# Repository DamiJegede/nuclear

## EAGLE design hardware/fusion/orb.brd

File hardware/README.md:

## Current routed engineering draft — Rev D (2026-10-29)

Four-layer routing and antenna clearance clipped to the circular edge. **Fusion confirms zero airwires, zero copper-clearance errors and zero overlap errors.** Saved as **Orb Mainboard Rev D - Routed**. Two matched-length errors and forty wire-stub warnings remain; this is not a fabrication release. See [routing-rev-d.md](design/routing-rev-d.md) for current checks, required filled-and-capped vias and fabrication holds. Routing is reproducible through `src/routing.json`; do not regenerate from older Rev C sources. Earlier sections below record the previous revision.

# Current board revision: C

U1 is now ESP32-C3FH4X with a separate 40 MHz crystal and Johanson 2450AT18D0100001E SMT antenna. GPIO assignments and 23-LED count are preserved. See [RF redesign notes](design/rf-redesign.md). Generated files are the revised schematic and placement draft; the Rev B Fusion archive remains an earlier routing checkpoint.

# Orb hardware

The Orb main board: a 69 mm round board with an ESP32-C3-MINI-1-N4X, a PN7161 NFC controller, 23 WS2812B LEDs on a ring (R31.5), a MAX98357A amplifier, USB-C, and a 1-cell Li-ion charger, gauge and 3.3 V supply. Product decisions are in `docs/ORB.md`; this folder turns them into files you can open in Fusion.

## Import into Fusion

Written for Autodesk Fusion (Electronics). The files are in the Eagle XML format, which Fusion imports. The initial files were imported and linked in Fusion on 2026-10-29. The source revision below corrects problems found by the initial Fusion DRC; confirm the revised import and its DRC before release.

1. Fusion's Data Panel, **Upload**, and choose all three files from `hardware/fusion/`: `orb.lbr`, `orb.sch`, `orb.brd`. (Or File, Open, Open from my computer.)
2. Open `orb.sch`: 122 parts in functional blocks (MCU, USB, power, I2C, NFC, audio, LED rail, LED ring), every connection a named net.
3. Open `orb.brd`: the R34.5 mm outline and the layout below, all connections unrouted (ratsnest). `design/layout.png` is a picture of it.
4. Run ERC on the schematic and DRC on the board. Expect warnings: the footprint list in `design/open-items.md` is the reason for most.

## Layout revision 2026-10-29

- **LEDs:** 23 on R31.5, clockwise: upper right 65/52/39/26/13 degrees; lower arc -12 to -168 degrees in 13-degree steps (13 LEDs); upper left 167/154/141/128/115 degrees. Five on each upper side, with a 50-degree opening around USB-C at 12 o'clock. Measured minimum LED copper-pad gap: 0.309 mm (the former 12-degree arrangement overlapped).
- **USB-C:** remains underneath at 12 o'clock. Manufacturer drawing-based pad rows and slotted mounts replace the former SMD-only approximation. The manufacturer's front-face/PCB-edge reference is aligned at y=34.5; the former guessed 2.7 mm overhang is removed. Mount holes and their copper annuli reserve clearance on both faces. Slot plating/geometry and the enclosure opening still need fabrication/mechanical review.
- **Speaker:** mounted directly on the PCB as requested; a 15 x 11 mm body, with 19.5 x 12 mm total assembly allowance, is reserved at (0,9). This part uses solder pads and adhesive retention with short hand-soldered leads; a reflow mounting specification is not available. Polymer capacitors move to (-10,21.6)/(10,21.6), battery header to (0,20.5), MCU to (-9.4,-5.2). Smaller parts are repacked around these bodies.
- **FPC:** Hirose FH19C-4S-0.5SH(10), 0.5 mm pitch, bottom contacts, 0.2 mm tail. Mouth +y, origin (0,-20.5); positions 2/3 carry RF, 1/4 remain open. Confirm tail fabrication stack-up.
- **Preserved constraints:** 69 mm circular board, M2 holes at (+-32,0), pedestal slots at (+-27.4,0), pedestal keep-outs on both sides, clear branding area below y=-22.5. Battery stays underneath; the LED decouplers are underneath their LEDs. The top USB gap now leaves their through mounts clear.
- `src/layout.py` checks courtyards and mechanical restrictions. `design/geometry-audit.json` records the separate source-file copper audit. Fusion DRC/ERC and actual routing are still required; this is an engineering draft.

## What is solid and what is not

- **Solid:** pin and pad numbers of every IC, taken from the manufacturers' datasheets (ESP32-C3-MINI-1 v2.2, PN7160/PN7161 rev 4.2, BQ2407x, TPS63802, TPS22918, SN74LV1T34, MAX98357A, MAX17048); all connections; the GPIO plan; the resistor arithmetic (3.3 V divider, charge and input limits, VBUS sense). `src/check.py` and `src/verify_eagle.py` prove those.
- **Still preliminary:** USB-C plated-slot fabrication, speaker assembly/retention, generic NFC/amplifier/gauge footprints, LED revision and passive MPN/height selection require review. Manufacturer-derived overrides replace U1/J1/J2/J3/U4/U5 geometry; the NFC matching network and crystal remain TBD. See `design/open-items.md`.
- **Still requires engineering validation:** antenna tuning and certification.

## Files

| Path | What |
| --- | --- |
| `fusion/orb.lbr`, `orb.sch`, `orb.brd` | Generated. Do not edit by hand; edit `src/design.py` and rebuild |
| `components/` | 19 downloaded standalone STEP models, source manifest and licenses; see `components/README.md` for generic/provisional models and unresolved parts |
| `bom/bom.csv` | Bill of materials: part, quantity, references, value, package, manufacturer, MPN, status (specified / generic / TBD) |
| `design/pin-plan.md` | GPIO assignments with the datasheet reasons |
| `design/power.md` | Power tree, part choices and the current budget |
| `design/open-items.md` | What must still happen before fabrication |
| `src/design.py` | The single source of truth: part types (pins by datasheet), instances, nets, GPIO plan |
| `src/check.py` | Checks the design (pads, nets, GPIOs, strapping rules, arithmetic) |
| `src/layout.py`, `src/preview.py` | Place the parts, check the board rules, draw `design/layout.png` |
| `src/eagle.py`, `build.py` | Write the Fusion files, BOM and pin plan |
| `src/verify_eagle.py` | Re-reads the Fusion files and compares them with the design |

Rebuild: `npm run hardware:build` (runs the check, writes everything, then verifies the written files).

## Decisions made while building this (change them in `design.py`)

- **PN7161 on I2C** (order code PN7161A1HN/C101E), sharing the bus with the fuel gauge, because the module exposes only 15 GPIOs and the board needs 14 signals; SPI would not fit. The firmware's four SPI pin constants are gone.
- **BQ24074** charger with power path (VSYS follows the battery, 4.4 V on USB), **TPS63802** buck-boost for 3.3 V, **TPS22918** switch on the LED rail so 28 idle LEDs do not drain the battery, and an **SN74LV1T34** level translator so the 3.3 V data reaches the LEDs' input threshold at VLED.
- No battery NTC: the charger's TS pin is held with a fixed 10 k resistor, as docs/ORB.md says the pack has none.
- Gauge charge detection and the charger's /CHG line both exist; the firmware can use either.

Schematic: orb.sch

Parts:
ANT1: 2450AT18D0100001E; JOHANSON_2450AT18D
C1, C5, C6, C8, C9, C10, C29, C31: 10uF; C0603
C2, C7, C11, C14, C16, C17, C18, C19, C30, C35, C36, C101, C102, C103, C104, C105, C106, C107, C108, C109, C110, C111, C112, C113, C114, C115, C116, C117, C118, C119, C120, C121, C122, C123: 100nF; C0402
C3, C15, C34, C37, C38: 1uF; C0402
C4, C12, C13: 4.7uF; C0603
C20, C21: 12pF; C0402
C22, C23, C24, C25, C26, C27, C28: TBD; C0402
C32, C33: 100uF; CPOL7343
C39: 10nF; C0402
C40, C41: 16pF; C0402
C42, C43, C44, C45: 1pF; C0402
D1: USBLC6-2SC6; SOT23_6
J1: USB-C; USBC24_TE2345986
J2: BAT; JST_S2B_PH_SM4_TB
J3: NFC antenna; FPC4_PLACEHOLDER
L1: 0.47uH; L2016
L2, L3: TBD; L0402
L4: 2nH; L0402
L5: 24nH; L0402
L6: 2.4nH; L0402
LED1, LED2, LED3, LED4, LED5, LED6, LED7, LED8, LED9, LED10, LED11, LED12, LED13, LED14, LED15, LED16, LED17, LED18, LED19, LED20, LED21, LED22, LED23: WS2812B; WS2812B_5050
R1, R10: 10k; R0402
R3, R12, R18, R19, R20: 100k; R0402
R4, R5: 5.1k; R0402
R6: 120k; R0402
R7: 220k; R0402
R8: 1.8k; R0402
R9: 1.13k; R0402
R11: 560k; R0402
R13, R14: 2.2k; R0402
R15, R16: TBD; R0402
R17: 2k; R0402
R21: 33; R0402
R22, R23: 0; R0402
SPK1: CMS-151103-088SP; SPK_PADS
TP1: EN; TP1MM
TP2: BOOT; TP1MM
TP3: 3V3; TP1MM
TP4: GND; TP1MM
TP5: VSYS; TP1MM
TP6: VBAT; TP1MM
U1: ESP32-C3FH4X; ESP32C3_QFN32
U2: PN7161A1HN/C101E; HVQFN40_6X6
U3: MAX17048G+T10; TDFN8_2X2
U4: BQ24074RGTR; VQFN16_3X3
U5: TPS63802DLAR; VSON10_2X3
U6: MAX98357AETE+T; TQFN16_3X3
U7: TPS22918DBVR; SOT23_6
U8: SN74LV1T34DBVR; SOT23_5
Y1: 27.12MHz; XTAL2016
Y2: 40MHz; ABM8_3225

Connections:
3V3: C1.1, C2.1, C9.1, C10.1, C19.1, C35.1, C36.1, C38.1, C39.1, L4.1, R1.1, R3.1, R11.1, R13.1, R14.1, TP3.1, U1.11 (VDD_RTC), U1.17 (VDD_CPU), U1.31 (VDDA), U1.32 (VDDA), U2.6 (VDD_PAD), U5.6 (VOUT)
AMP_SD: R17.1, U1.28 (TXD0_IO21)
AMP_SD_R: R17.2, R18.1, U6.4 (SD_MODE)
ANT_FEED: ANT1.1 (FEED), C45.1, R22.2
ANT_GND_TUNE: ANT1.3 (TUNE), R23.1
BOOT: TP2.1, U1.15 (IO9)
CC1: J1.A5 (CC1), R4.1
CC2: J1.B5 (CC2), R5.1
CHG_STATUS: R3.2, U1.6 (IO2), U4.9 (CHG)
EN: C3.1, R1.2, TP1.1, U1.7 (EN)
ESP_RF_CHIP: C42.1, L6.1, U1.1 (LNA_IN)
ESP_VDD_RF: C34.1, L4.2, U1.2 (VDD_RF), U1.3 (VDD_RF)
ESP_VDD_SPI: C37.1, U1.18 (VDD_SPI)
ESP_XTAL_DRIVE: C40.1, L5.2, Y2.1
ESP_XTAL_N: C41.1, U1.29 (XTAL_N), Y2.3 (2)
ESP_XTAL_P: L5.1, U1.30 (XTAL_P)
FB_3V3: R11.2, R12.1, U5.4 (FB)
GND: ANT1.2 (GND), ANT1.4 (GND), C1.2, C2.2, C3.2, C4.2, C5.2, C6.2, C7.2, C8.2, C9.2, C10.2, C11.2, C12.2, C13.2, C14.2, C15.2, C16.2, C17.2, C18.2, C19.2, C20.2, C21.2, C22.2, C23.2, C29.2, C30.2, C31.2, C32.2 (N), C33.2 (N), C34.2, C35.2, C36.2, C37.2, C38.2, C39.2, C40.2, C41.2, C42.2, C43.2, C44.2, C45.2, C101.2, C102.2, C103.2, C104.2, C105.2, C106.2, C107.2, C108.2, C109.2, C110.2, C111.2, C112.2, C113.2, C114.2, C115.2, C116.2, C117.2, C118.2, C119.2, C120.2, C121.2, C122.2, C123.2, D1.2 (GND), J1.A1 (GND), J1.A12 (GND), J1.B1 (GND), J1.B12 (GND), J1.S1 (SHIELD), J1.S2 (SHIELD), J1.S3 (SHIELD), J1.S4 (SHIELD), J2.2 (BAT_N), J2.S1 (MECH), J2.S2 (MECH), J3.M1 (MECH), J3.M2 (MECH), LED1.3 (VSS), LED2.3 (VSS), LED3.3 (VSS), LED4.3 (VSS), LED5.3 (VSS), LED6.3 (VSS), LED7.3 (VSS), LED8.3 (VSS), LED9.3 (VSS), LED10.3 (VSS), LED11.3 (VSS), LED12.3 (VSS), LED13.3 (VSS), LED14.3 (VSS), LED15.3 (VSS), LED16.3 (VSS), LED17.3 (VSS), LED18.3 (VSS), LED19.3 (VSS), LED20.3 (VSS), LED21.3 (VSS), LED22.3 (VSS), LED23.3 (VSS), R4.2, R5.2, R7.2, R8.2, R9.2, R10.2, R12.2, R18.2, R19.2, R20.2, R23.2, TP4.1, U1.33 (GND), U2.1 (I2C_ADR0), U2.2 (DWL_REQ), U2.3 (I2C_ADR1), U2.4 (VSS_PAD), U2.9 (VSS_A), U2.20 (VSS_TX), U2.39 (WKUP_REQ), U2.41 (VSS), U3.1 (CTG), U3.4 (GND), U3.6 (QSTRT), U3.9 (GND), U4.4 (CE), U4.6 (EN1), U4.8 (VSS), U4.17 (VSS), U5.2 (MODE), U5.3 (AGND), U5.8 (GND), U6.3 (GND), U6.11 (GND), U6.15 (GND), U6.17 (GND), U7.2 (GND), U8.3 (GND), Y1.2 (GND_A), Y1.4 (GND_B), Y2.2 (GND_A), Y2.4 (GND_B)
I2C_SCL: R14.2, U1.10 (IO5), U2.7 (SCL), U3.7 (SCL)
I2C_SDA: R13.2, U1.9 (IO4), U2.5 (SDA), U3.8 (SDA)
I2S_BCLK: U1.13 (IO7), U6.16 (BCLK)
I2S_DIN: U1.27 (RXD0_IO20), U6.1 (DIN)
I2S_LRCLK: U1.16 (IO10), U6.14 (LRCLK)
ILIM: R8.1, U4.12 (ILIM)
ISET: R9.1, U4.16 (ISET)
LED_CHAIN_1: LED1.2 (DOUT), LED2.4 (DIN)
LED_CHAIN_2: LED2.2 (DOUT), LED3.4 (DIN)
LED_CHAIN_3: LED3.2 (DOUT), LED4.4 (DIN)
LED_CHAIN_4: LED4.2 (DOUT), LED5.4 (DIN)
LED_CHAIN_5: LED5.2 (DOUT), LED6.4 (DIN)
LED_CHAIN_6: LED6.2 (DOUT), LED7.4 (DIN)
LED_CHAIN_7: LED7.2 (DOUT), LED8.4 (DIN)
LED_CHAIN_8: LED8.2 (DOUT), LED9.4 (DIN)
LED_CHAIN_9: LED9.2 (DOUT), LED10.4 (DIN)
LED_CHAIN_10: LED10.2 (DOUT), LED11.4 (DIN)
LED_CHAIN_11: LED11.2 (DOUT), LED12.4 (DIN)
LED_CHAIN_12: LED12.2 (DOUT), LED13.4 (DIN)
LED_CHAIN_13: LED13.2 (DOUT), LED14.4 (DIN)
LED_CHAIN_14: LED14.2 (DOUT), LED15.4 (DIN)
LED_CHAIN_15: LED15.2 (DOUT), LED16.4 (DIN)
LED_CHAIN_16: LED16.2 (DOUT), LED17.4 (DIN)
LED_CHAIN_17: LED17.2 (DOUT), LED18.4 (DIN)
LED_CHAIN_18: LED18.2 (DOUT), LED19.4 (DIN)
LED_CHAIN_19: LED19.2 (DOUT), LED20.4 (DIN)
LED_CHAIN_20: LED20.2 (DOUT), LED21.4 (DIN)
LED_CHAIN_21: LED21.2 (DOUT), LED22.4 (DIN)
LED_CHAIN_22: LED22.2 (DOUT), LED23.4 (DIN)
LED_DATA_0: LED1.4 (DIN), R21.2
LED_DATA_3V3: R20.1, U1.12 (IO6), U8.2 (A)
LED_DATA_BUF: R21.1, U8.4 (Y)
LED_EN: R19.1, U1.8 (IO3), U7.3 (ON)
NFC_ANT_N: C25.2, C26.2, C28.1, J3.3
NFC_ANT_P: C24.2, C26.1, C27.1, J3.2
NFC_EMC1: C22.1, C24.1, L2.2
NFC_EMC2: C23.1, C25.1, L3.2
NFC_IRQ: U1.4 (IO0), U2.8 (IRQ)
NFC_RXC1: C27.2, R15.1
NFC_RXC2: C28.2, R16.1
NFC_RXN: R16.2, U2.15 (RXN)
NFC_RXP: R15.2, U2.16 (RXP)
NFC_TX1: L2.1, U2.21 (TX1)
NFC_TX2: L3.1, U2.19 (TX2)
NFC_VDD: C15.1, C16.1, U2.26 (VDD_A), U2.27 (VDD), U2.31 (VDD_D)
NFC_VDDHF: C18.1, U2.25 (VDD_HF)
NFC_VEN: U1.5 (IO1), U2.10 (VEN)
NFC_VMID: C17.1, U2.17 (VDD_VMID)
NFC_XTAL1: C20.1, U2.30 (XTAL1), Y1.1
NFC_XTAL2: C21.1, U2.29 (XTAL2), Y1.3 (2)
RF_50OHM: C43.1, C44.1, L6.2, R22.1
SPK_N: SPK1.2 (N), U6.10 (OUTN)
SPK_P: SPK1.1, U6.9 (OUTP)
SW1: L1.1, U5.9 (L1)
SW2: L1.2, U5.7 (L2)
TS: R10.1, U4.1 (TS)
USB_DN: D1.4 (IO2_B), U1.25 (IO18)
USB_DN_J: D1.3 (IO2_A), J1.A7 (DN), J1.B7 (DN)
USB_DP: D1.6 (IO1_B), U1.26 (IO19)
USB_DP_J: D1.1 (IO1_A), J1.A6 (DP), J1.B6 (DP)
VBAT: C6.1, C7.1, J2.1 (BAT_P), TP6.1, U3.2 (CELL), U3.3 (VDD), U4.2 (BAT), U4.3 (BAT)
VBUS: C4.1, D1.5 (VBUS), J1.A4 (VBUS), J1.A9 (VBUS), J1.B4 (VBUS), J1.B9 (VBUS), R6.1, U4.13 (IN)
VBUS_SENSE: R6.2, R7.1, U1.14 (IO8)
VDD_TX: C13.1, C14.1, U2.14 (VDD_TX), U2.18 (TVDD_IN), U2.22 (TVDD_IN2)
VLED: C32.1, C33.1, C101.1, C102.1, C103.1, C104.1, C105.1, C106.1, C107.1, C108.1, C109.1, C110.1, C111.1, C112.1, C113.1, C114.1, C115.1, C116.1, C117.1, C118.1, C119.1, C120.1, C121.1, C122.1, C123.1, LED1.1 (VDD), LED2.1 (VDD), LED3.1 (VDD), LED4.1 (VDD), LED5.1 (VDD), LED6.1 (VDD), LED7.1 (VDD), LED8.1 (VDD), LED9.1 (VDD), LED10.1 (VDD), LED11.1 (VDD), LED12.1 (VDD), LED13.1 (VDD), LED14.1 (VDD), LED15.1 (VDD), LED16.1 (VDD), LED17.1 (VDD), LED18.1 (VDD), LED19.1 (VDD), LED20.1 (VDD), LED21.1 (VDD), LED22.1 (VDD), LED23.1 (VDD), U7.5 (QOD), U7.6 (VOUT), U8.5 (VCC)
VSYS: C5.1, C8.1, C11.1, C12.1, C29.1, C30.1, C31.1, TP5.1, U2.12 (VBAT2), U2.13 (VDD_UP), U2.28 (VBAT), U4.5 (EN2), U4.10 (OUT), U4.11 (OUT), U5.1 (EN), U5.10 (VIN), U6.7 (VDD), U6.8 (VDD), U7.1 (VIN)

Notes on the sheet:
Orb main board: generated from hardware/src/design.py, do not edit by hand

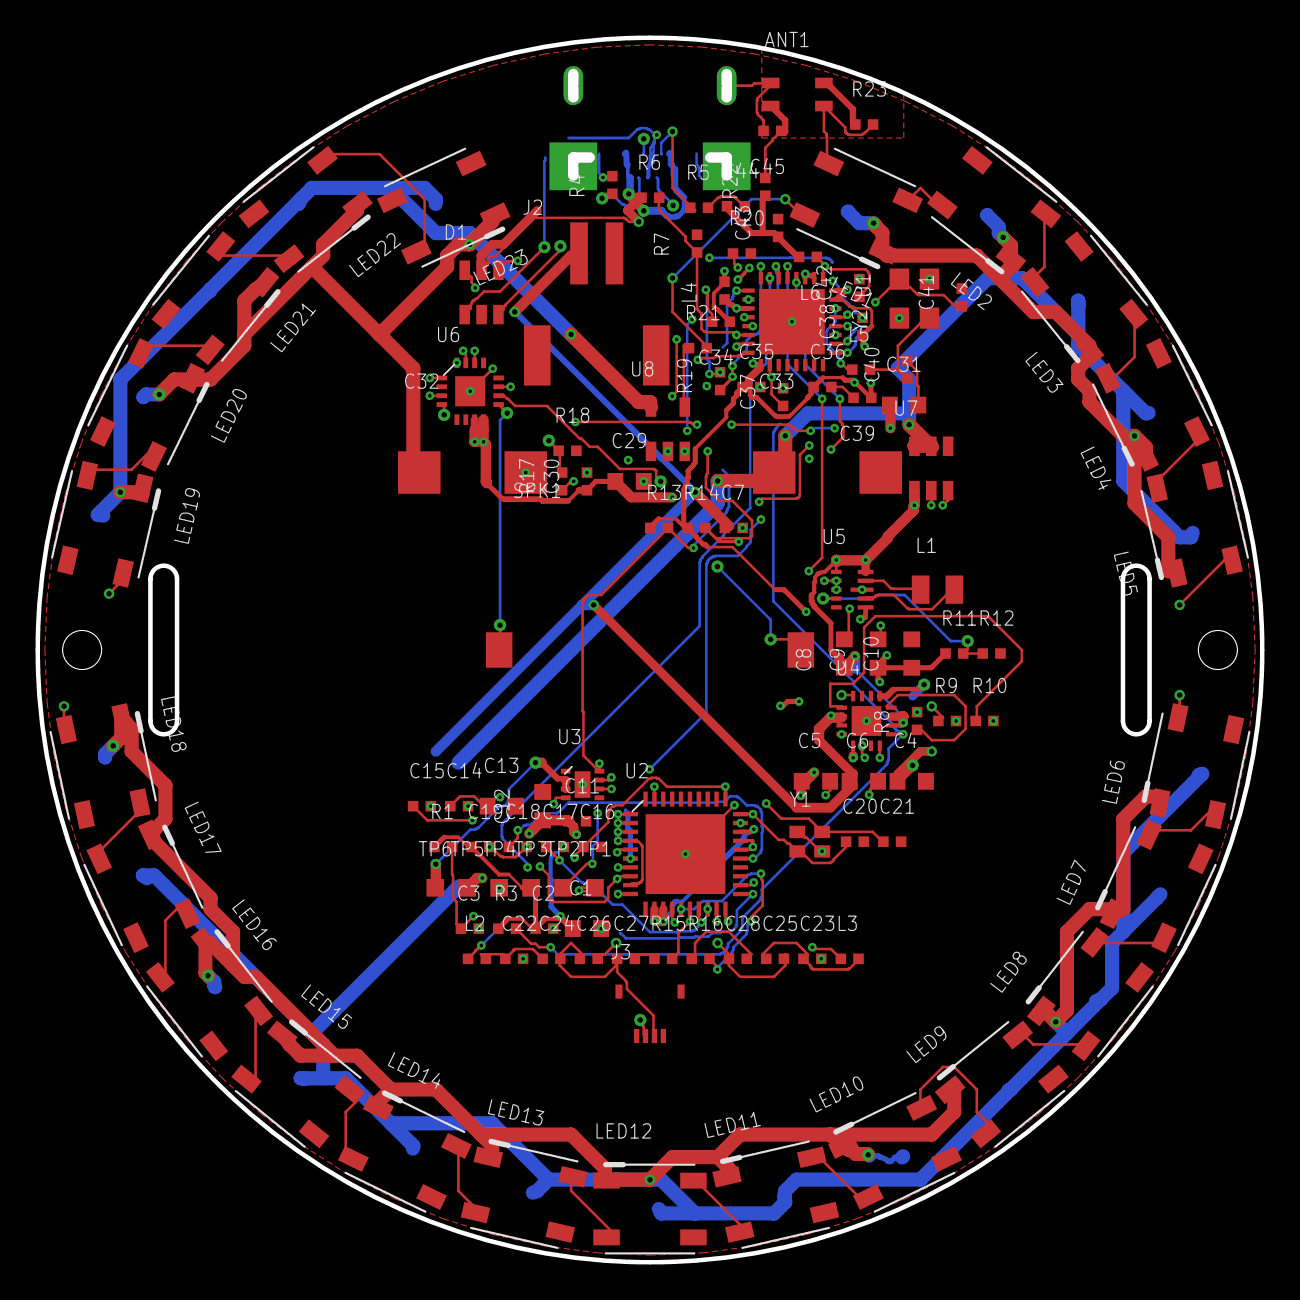
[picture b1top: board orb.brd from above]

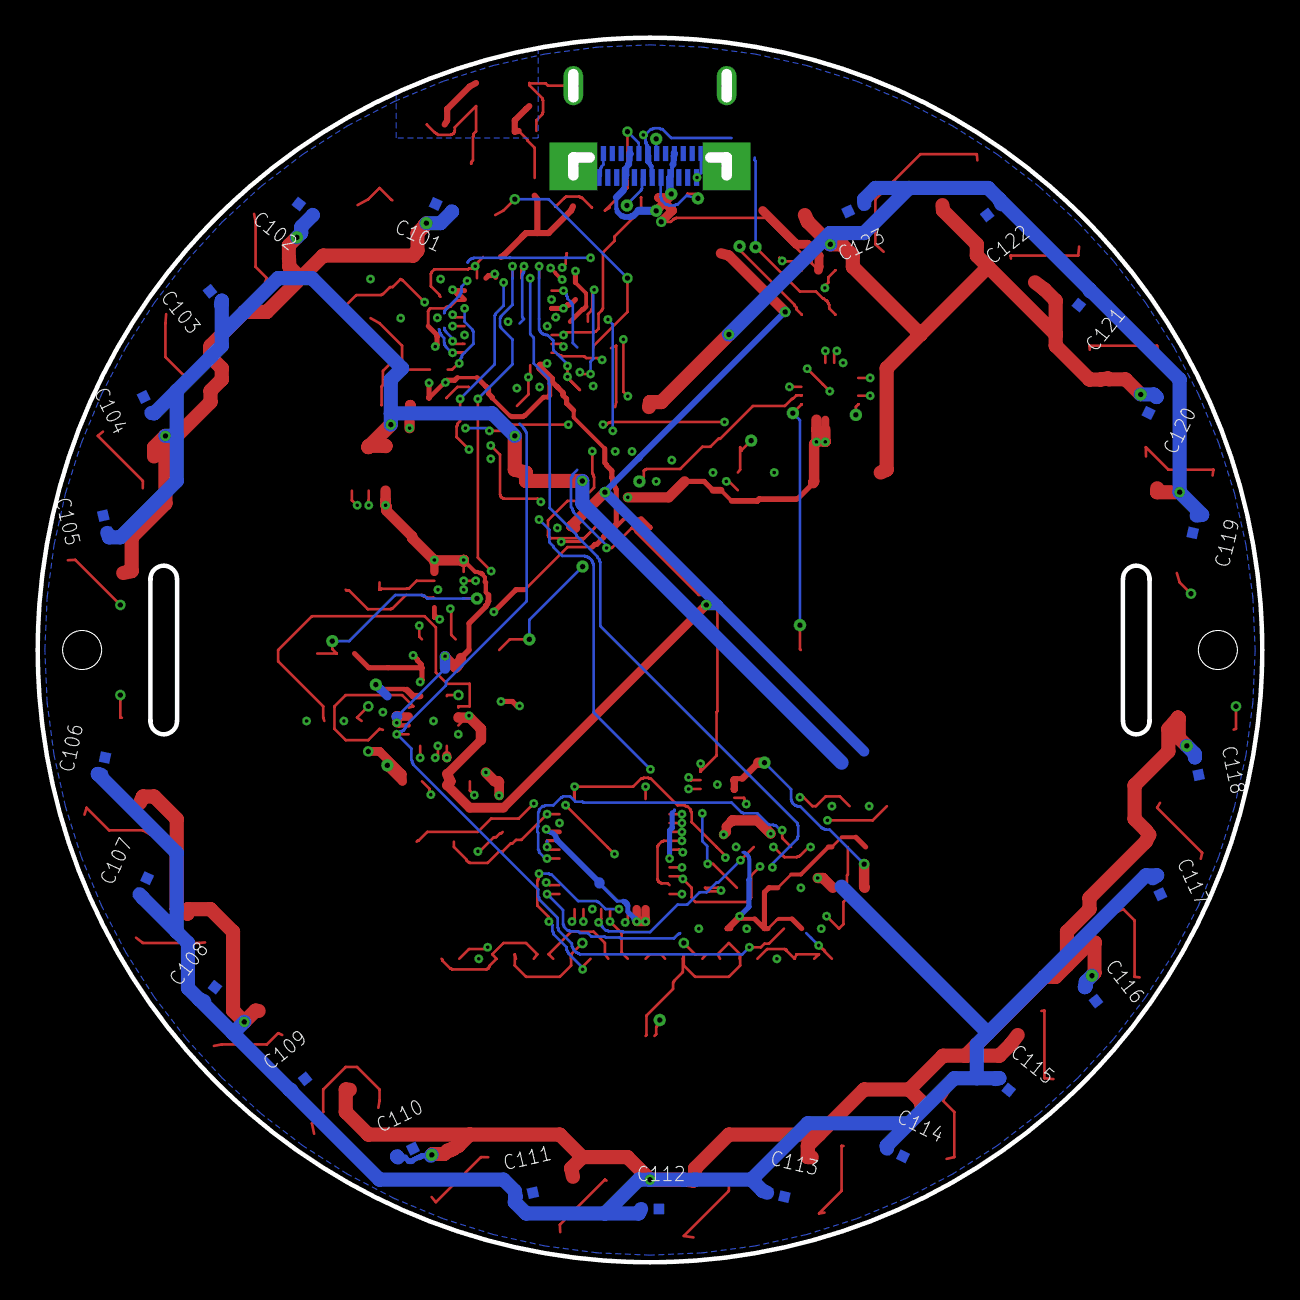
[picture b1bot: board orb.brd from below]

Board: 4 copper layers, 69.0 x 69.0 mm, 141 parts (24 on the bottom side), 84 nets.

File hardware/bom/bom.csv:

Type,Qty,References,Value,Description,Package,Manufacturer,MPN,Status
U,1,U1,ESP32-C3FH4X,"Espressif ESP32-C3FH4X, 4 MB in-package flash, QFN32 5 x 5 mm",ESP32C3_QFN32,Espressif,ESP32-C3FH4X,specified
U,1,U2,PN7161A1HN/C101E,NXP PN7161A1HN NFC controller (I2C),HVQFN40_6X6,NXP,PN7161A1HN/C101E,specified
U,1,U3,MAX17048G+T10,Analog/Maxim MAX17048G+T10 fuel gauge (TDFN-8),TDFN8_2X2,Analog Devices (Maxim),MAX17048G+T10,specified
U,1,U4,BQ24074RGTR,TI BQ24074RGTR charger and power path (VQFN-16),VQFN16_3X3,Texas Instruments,BQ24074RGTR,specified
U,1,U5,TPS63802DLAR,TI TPS63802DLAR buck-boost 3.3 V (VSON-10),VSON10_2X3,Texas Instruments,TPS63802DLAR,specified
U,1,U6,MAX98357AETE+T,Analog/Maxim MAX98357AETE+T I2S Class D amplifier (TQFN-16),TQFN16_3X3,Analog Devices (Maxim),MAX98357AETE+T,specified
U,1,U7,TPS22918DBVR,TI TPS22918DBVR load switch (SOT-23-6),SOT23_6,Texas Instruments,TPS22918DBVR,specified
U,1,U8,SN74LV1T34DBVR,TI SN74LV1T34DBVR level-shifting buffer (SOT-23-5),SOT23_5,Texas Instruments,SN74LV1T34DBVR,specified
J,1,J1,USB-C,"TE Connectivity 2345986-1 USB-C receptacle (24 pads, USB 3.1 top mount, dual row SMT; only the USB 2.0 pads are used)",USBC24_TE2345986,TE Connectivity,2345986-1,specified
J,1,J2,BAT,JST S2B-PH-SM4-TB battery header,JST_S2B_PH_SM4_TB,JST,S2B-PH-SM4-TB,specified
J,1,J3,NFC antenna,"Hirose FH19C-4S-0.5SH(10), 0.5 mm pitch, 0.2 mm bottom-contact FPC",FPC4_PLACEHOLDER,Hirose,FH19C-4S-0.5SH(10),specified
Y,1,Y1,27.12MHz,Crystal,XTAL2016,,,TBD
Y,1,Y2,40MHz,Abracon ABM8 3.2 x 2.5 mm 40 MHz crystal,ABM8_3225,Abracon,ABM8-40.000MHZ-10-1-U-T,specified
D,1,D1,USBLC6-2SC6,ST USBLC6-2SC6 USB ESD protection (SOT-23-6),SOT23_6,STMicroelectronics,USBLC6-2SC6,specified
LED,23,"LED1, LED2, LED3, LED4, LED5, LED6, LED7, LED8, LED9, LED10, LED11, LED12, LED13, LED14, LED15, LED16, LED17, LED18, LED19, LED20, LED21, LED22, LED23",WS2812B,WS2812B addressable LED (5050; revision TBC),WS2812B_5050,Worldsemi,WS2812B,specified
L,1,L1,0.47uH,Power inductor,L2016,,,TBD
L,2,"L2, L3",TBD,Inductor,L0402,,,TBD
L,1,L4,2nH,Inductor,L0402,,,generic
L,1,L5,24nH,Inductor,L0402,,,generic
L,1,L6,2.4nH,Inductor,L0402,,,generic
C,8,"C1, C5, C6, C8, C9, C10, C29, C31",10uF,Capacitor,C0603,,,generic
C,34,"C2, C7, C11, C14, C16, C17, C18, C19, C30, C35, C36, C101, C102, C103, C104, C105, C106, C107, C108, C109, C110, C111, C112, C113, C114, C115, C116, C117, C118, C119, C120, C121, C122, C123",100nF,Capacitor,C0402,,,generic
C,2,"C20, C21",12pF,Capacitor,C0402,,,generic
C,7,"C22, C23, C24, C25, C26, C27, C28",TBD,Capacitor,C0402,,,TBD
C,5,"C3, C15, C34, C37, C38",1uF,Capacitor,C0402,,,generic
C,2,"C32, C33",100uF,Polymer capacitor,CPOL7343,,,generic
C,1,C39,10nF,Capacitor,C0402,,,generic
C,3,"C4, C12, C13",4.7uF,Capacitor,C0603,,,generic
C,2,"C40, C41",16pF,Capacitor,C0402,,,generic
C,2,"C42, C43",1pF,Capacitor,C0402,,,generic
C,2,"C44, C45",1pF,Capacitor,C0402,,,generic
R,2,"R1, R10",10k,Resistor,R0402,,,generic
R,1,R11,560k,Resistor,R0402,,,generic
R,2,"R13, R14",2.2k,Resistor,R0402,,,generic
R,2,"R15, R16",TBD,Resistor,R0402,,,TBD
R,1,R17,2k,Resistor,R0402,,,generic
R,1,R21,33,Resistor,R0402,,,generic
R,2,"R22, R23",0,Resistor,R0402,,,generic
R,5,"R3, R12, R18, R19, R20",100k,Resistor,R0402,,,generic
R,2,"R4, R5",5.1k,Resistor,R0402,,,generic
R,1,R6,120k,Resistor,R0402,,,generic
R,1,R7,220k,Resistor,R0402,,,generic
R,1,R8,1.8k,Resistor,R0402,,,generic
R,1,R9,1.13k,Resistor,R0402,,,generic
T,1,TP1,EN,Test pad,TP1MM,,,generic
T,1,TP2,BOOT,Test pad,TP1MM,,,generic
T,1,TP3,3V3,Test pad,TP1MM,,,generic
T,1,TP4,GND,Test pad,TP1MM,,,generic
T,1,TP5,VSYS,Test pad,TP1MM,,,generic
T,1,TP6,VBAT,Test pad,TP1MM,,,generic
A,1,ANT1,2450AT18D0100001E,"Johanson 2450AT18D0100001E 2.4 GHz SMT antenna, thin-edge reference layout",JOHANSON_2450AT18D,Johanson Technology,2450AT18D0100001E,specified
S,1,SPK1,CMS-151103-088SP,Speaker CMS-151103-088SP (wire or pad connection),SPK_PADS,CUI Devices,CMS-151103-088SP,specified

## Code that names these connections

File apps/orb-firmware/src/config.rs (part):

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/// Enable for the LED power rail (TPS22918): 23 idle LEDs would draw about 23 mA, so the rail is off unless a pattern is showing.
pub const LED_ENABLE_PIN: Option<u8> = Some(3);
/// The PN7161 is the I2C version (PN7161A1HN/C101E): there are no SPI pins. It shares the I2C bus with the fuel gauge.
pub const NFC_IRQ_PIN: Option<u8> = Some(0);
pub const NFC_VEN_PIN: Option<u8> = Some(1);
pub const AUDIO_BCLK_PIN: Option<u8> = Some(7);
pub const AUDIO_LRCLK_PIN: Option<u8> = Some(10);
/// GPIO20 (U0RXD): UART0 is not used, the console is on native USB.
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/// GPIO2 (a strapping pin): the BQ24074 /CHG output, low while charging, with a 100 k pull-up.
pub const CHARGE_STATUS_PIN: Option<u8> = Some(2);
/// The shared I2C bus: PN7161 and MAX17048.
pub const I2C_SDA_PIN: Option<u8> = Some(4);
pub const I2C_SCL_PIN: Option<u8> = Some(5);
/// 7-bit addresses: PN7161 with I2C_ADR0 = I2C_ADR1 = GND, and the MAX17048.
pub const NFC_I2C_ADDRESS: u8 = 0x28;
pub const FUEL_GAUGE_I2C_ADDRESS: u8 = 0x36;
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    use super::*;

    const ASSIGNED: [Option<u8>; 12] = [
        LED_DATA_PIN, LED_ENABLE_PIN, NFC_IRQ_PIN, NFC_VEN_PIN, AUDIO_BCLK_PIN, AUDIO_LRCLK_PIN, AUDIO_DATA_PIN, AUDIO_SHUTDOWN_PIN, USB_POWER_SENSE_PIN,
        CHARGE_STATUS_PIN, I2C_SDA_PIN, I2C_SCL_PIN,
    ];

    #[test]
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
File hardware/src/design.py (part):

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add("C2", "C", "100nF", {"1": "3V3", "2": "GND"}, group="mcu")
add("R1", "R", "10k", {"1": "3V3", "2": "EN"}, group="mcu", note="EN pull-up (datasheet: R=10k, C=1uF RC delay)")
add("C3", "C", "1uF", {"1": "EN", "2": "GND"}, group="mcu")
add("R3", "R", "100k", {"1": "3V3", "2": "CHG_STATUS"}, group="mcu", note="Pull-up for BQ24074 /CHG (open drain) and for GPIO2, which the datasheet recommends pulling high")
add("TP1", "TP", "EN", {"TP": "EN"}, group="mcu", note="Reset pad: short to GND to reset")
add("TP2", "TP", "BOOT", {"TP": "BOOT"}, group="mcu", note="IO9: short to GND at reset for download mode (USB-JTAG/serial)")
add("TP3", "TP", "3V3", {"TP": "3V3"}, group="mcu")
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add("C33", "CPOL", "100uF", {"P": "VLED", "N": "GND"}, group="led")
add("U8", "SN74LV1T34", "SN74LV1T34DBVR", {"A": "LED_DATA_3V3", "VCC": "VLED", "GND": "GND", "Y": "LED_DATA_BUF"}, "SN74LV1T34DBVR", "Texas Instruments", group="led", nc=NC_BUF,
    note="Single-supply translator: 3.3 V input, output swings to VLED, so the data meets the LED's 0.7 x VDD input threshold")
add("R20", "R", "100k", {"1": "LED_DATA_3V3", "2": "GND"}, group="led", note="Keeps the input low while the MCU pin floats")
add("R21", "R", "33", {"1": "LED_DATA_BUF", "2": "LED_DATA_0"}, group="led", note="Series damping at the first LED")
N_LED = 23   # five LEDs on each upper side, thirteen below; see layout.py
for i in range(1, N_LED + 1):
    din = "LED_DATA_0" if i == 1 else f"LED_CHAIN_{i - 1}"
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PIN_PLAN = OrderedDict([
    (0,  ("NFC_IRQ", "in", "PN7161 interrupt, push-pull, active high by default. RTC pad: can wake from deep sleep")),
    (1,  ("NFC_VEN", "out", "PN7161 hardware enable (VIH 1.1 V). RTC pad")),
    (2,  ("CHG_STATUS", "in", "BQ24074 /CHG (open drain, low while charging) with a 100k pull-up. Strapping pin: the pull-up keeps it high at reset unless charging, and the datasheet says GPIO2 does not decide the boot mode")),
    (3,  ("LED_EN", "out", "TPS22918 enable for the LED rail, 100k pull-down. RTC pad")),
    (4,  ("I2C_SDA", "io", "Shared bus: PN7161 (0x28) and MAX17048 (0x36). Default JTAG pad, unused (USB-JTAG is on 18/19)")),
    (5,  ("I2C_SCL", "io", "Shared bus. Default JTAG pad, unused")),
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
